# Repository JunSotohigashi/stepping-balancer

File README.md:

# stepping-balancer
 Nucleo制御/ステッピングモータ駆動の二輪倒立振子ロボット

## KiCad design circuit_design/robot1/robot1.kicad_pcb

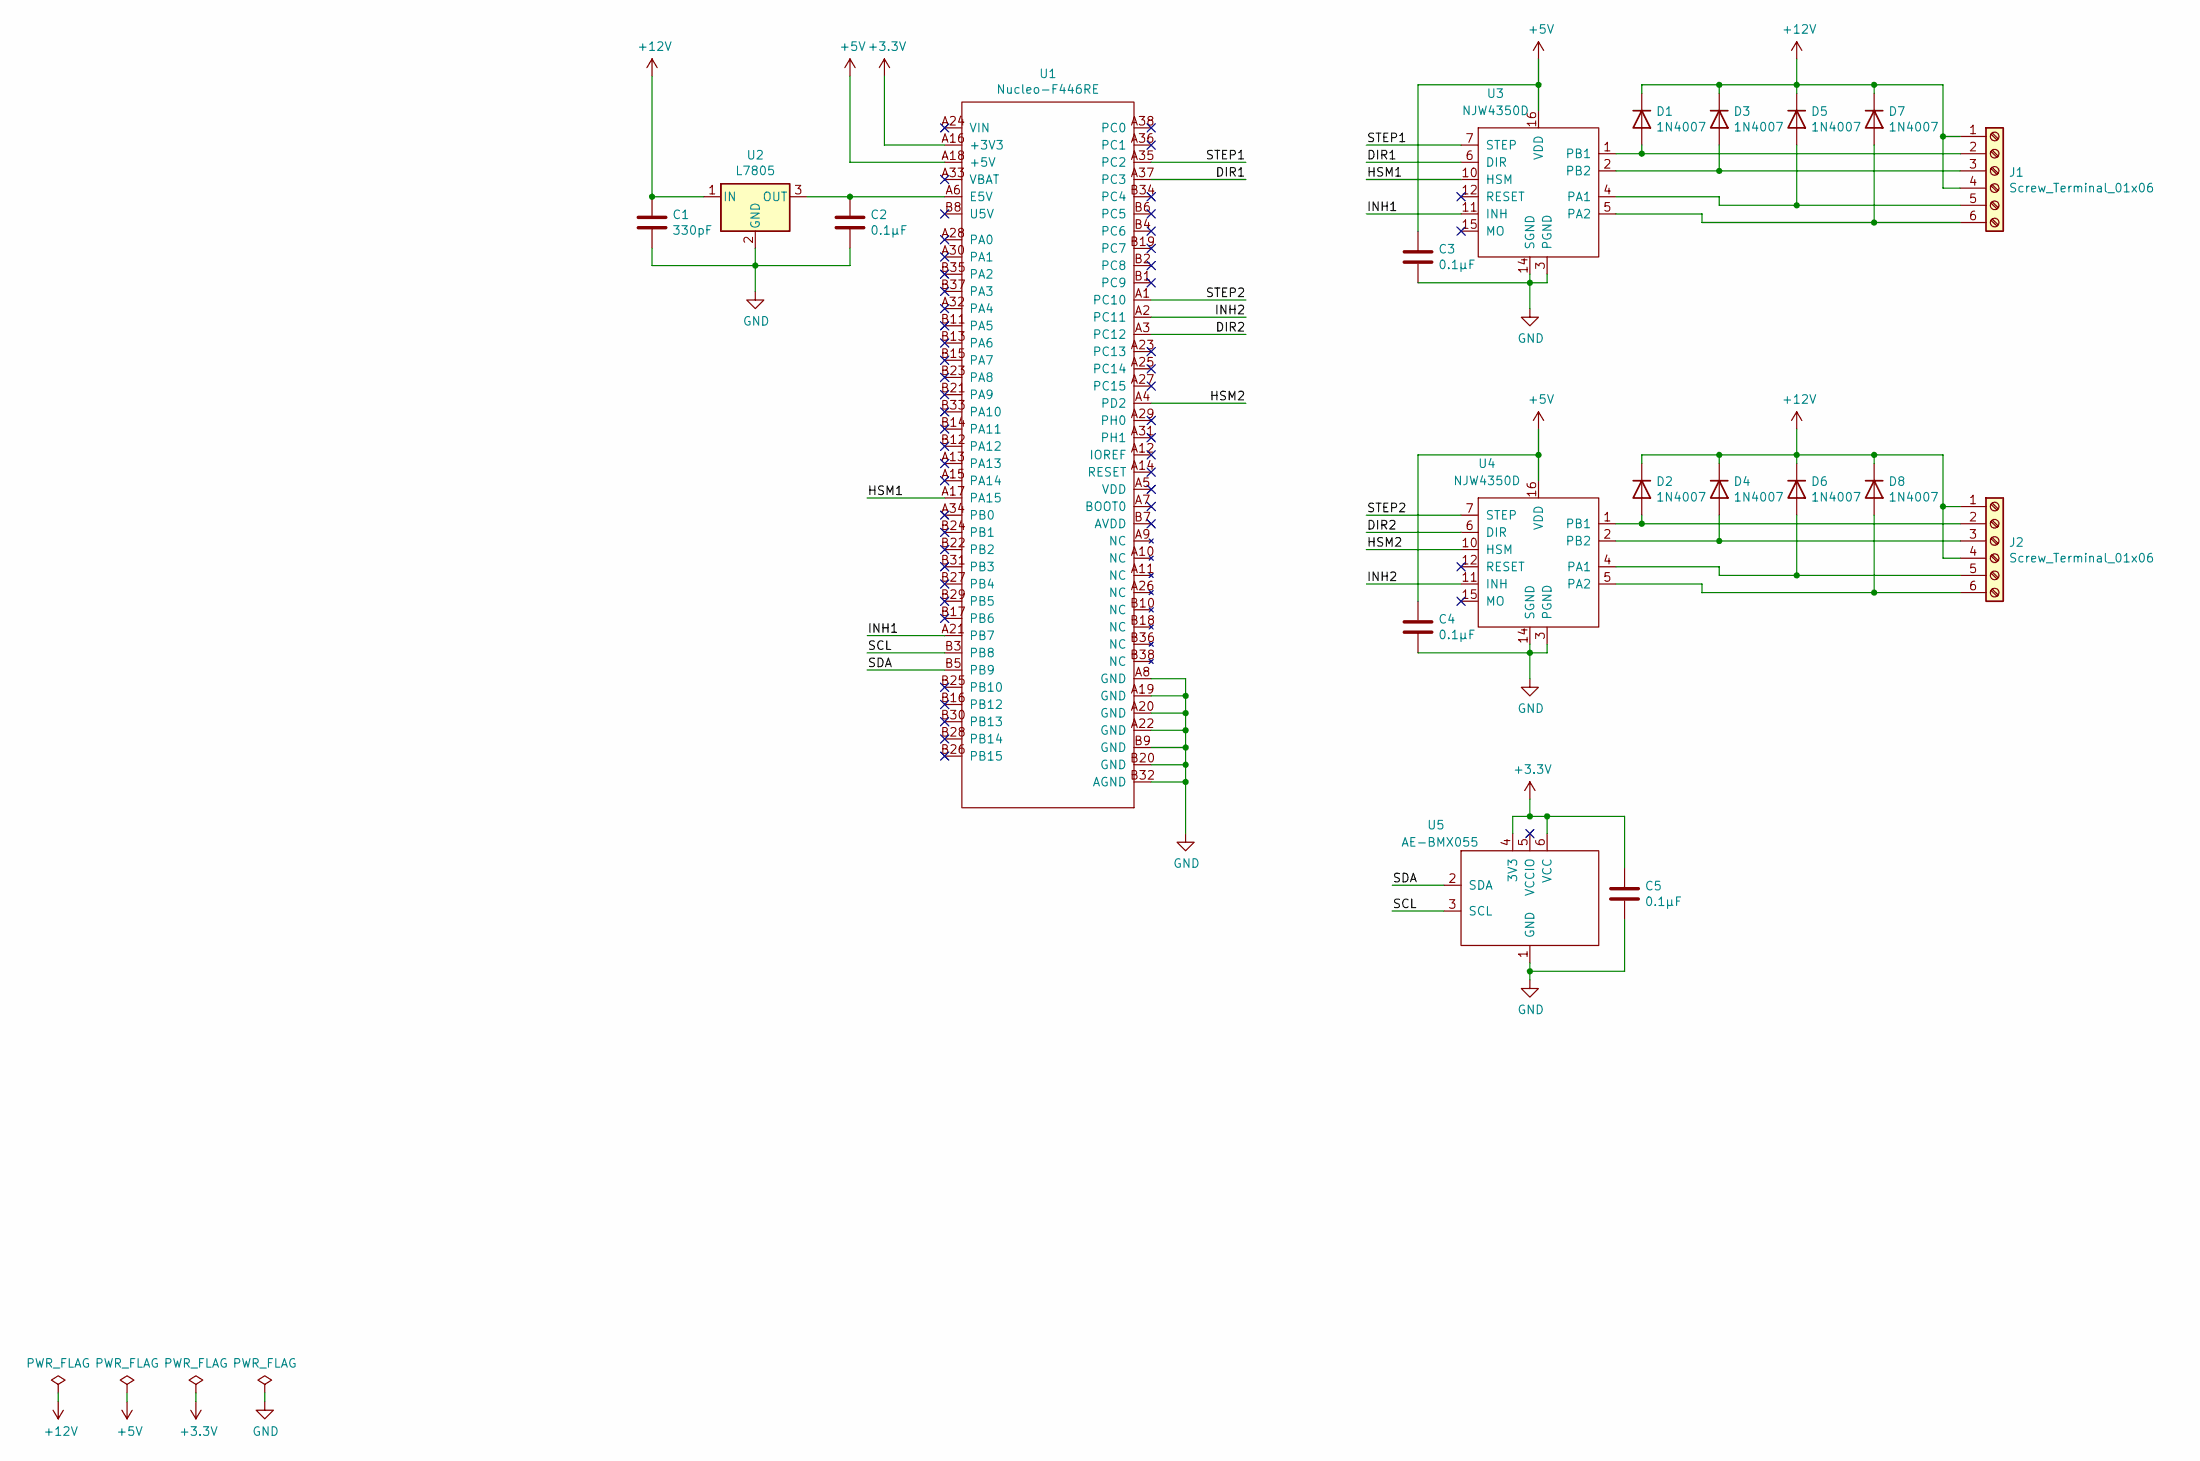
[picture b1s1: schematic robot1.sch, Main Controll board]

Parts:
C1: 330pF; CP_Axial_L10.0mm_D4.5mm_P15.00mm_Horizontal
C2, C3, C4, C5: 0.1μF; CP_Axial_L10.0mm_D4.5mm_P15.00mm_Horizontal
D1, D2, D3, D4, D5, D6, D7, D8: 1N4007; D_DO-41_SOD81_P10.16mm_Horizontal
J1, J2: Screw_Terminal_01x06; TerminalBlock_bornier-6_P5.08mm
U1: Nucleo-F446RE
U2: L7805; TO-3P-3_Horizontal_TabUp
U3, U4: NJW4350D; DIP-16_W7.62mm
U5: AE-BMX055; DIP-6_W7.62mm

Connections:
+3V3: C5.1, U1.A16 (+3V3), U5.4 (3V3), U5.6 (VCC)
+5V: C3.1, C4.1, U1.A18 (+5V), U3.16 (VDD), U4.16 (VDD)
+12V: C1.1, D1.1 (K), D2.1 (K), D3.1 (K), D4.1 (K), D5.1 (K), D6.1 (K), D7.1 (K), D8.1 (K), J1.1, J1.4, J2.1, J2.4, U2.1 (IN)
/DIR1: U1.A37 (PC3), U3.6 (DIR)
/DIR2: U1.A3 (PC12), U4.6 (DIR)
/HSM1: U1.A17 (PA15), U3.10 (HSM)
/HSM2: U1.A4 (PD2), U4.10 (HSM)
/INH1: U1.A21 (PB7), U3.11 (INH)
/INH2: U1.A2 (PC11), U4.11 (INH)
/SCL: U1.B3 (PB8), U5.3 (SCL)
/SDA: U1.B5 (PB9), U5.2 (SDA)
/STEP1: U1.A35 (PC2), U3.7 (STEP)
/STEP2: U1.A1 (PC10), U4.7 (STEP)
GND: C1.2, C2.2, C3.2, C4.2, C5.2, U1.A8 (GND), U1.A19 (GND), U1.A20 (GND), U1.A22 (GND), U1.B9 (GND), U1.B20 (GND), U1.B32 (AGND), U2.2 (GND), U3.3 (PGND), U3.14 (SGND), U4.3 (PGND), U4.14 (SGND), U5.1 (GND)
unnamed: C2.1, U1.A6 (E5V), U2.3 (OUT)
unnamed: D1.2 (A), J1.2, U3.1 (PB1)
unnamed: D2.2 (A), J2.2, U4.1 (PB1)
unnamed: D3.2 (A), J1.3, U3.2 (PB2)
unnamed: D4.2 (A), J2.3, U4.2 (PB2)
unnamed: D5.2 (A), J1.5, U3.4 (PA1)
unnamed: D6.2 (A), J2.5, U4.4 (PA1)
unnamed: D7.2 (A), J1.6, U3.5 (PA2)
unnamed: D8.2 (A), J2.6, U4.5 (PA2)

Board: 2 copper layers, 20 parts (0 on the bottom side), 23 nets, no tracks yet.

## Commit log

2022-12-27 [add]Initial upload
